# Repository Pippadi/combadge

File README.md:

# combadge [Work in Progress]

A Star Trek combadge built with the ESP32-S3.

> No copyright infringement is intended.
> This is simply a personal endeavor for fun and learning.

## Details

- Hardware and electronics: [hardware/pcb](hardware/pcb)
- Main ESP32 firmware: [software/combadge](software/combadge)
- Audio bridge: [software/bridge](software/bridge)
- 3D-printable enclosure: [hardware/enclosure](hardware/enclosure)
- Nuggets for testing: [software/test](software/test)
- Helpful scripts/tools: [software/tools](software/tools)

This is pretty much the entire directory tree. Happy exploring!

## Goals

Hardware has now been verified to work.

Some kind of basic walkie-talkie functionality is in the works, built on top of a custom Combadge Real-time Audio Protocol.
[WebRTC](https://webrtc.org) or [Matrix](https://matrix.org) support is a goal for the distant future.

Ahead of this, the roadmap is largely undecided. Capable hardware leaves great scope for software.

## Motivations

This is a hobby project I am pursuing in order to broaden my knowledge and experience with embedded electronics and programming.
And of course, to end up with a combadge better than the ones they used on TV (I believe those are just molded and painted resin).
Please bear in mind that I am a beginner, especially when it comes to the electronics (remember that before you plug the batteries in).

## Community

Suggestions, tips, and contributions are welcome!
I hope that with some (of your?) time and effort, this combadge can grow to become more useful than a block of resin, while still retaining the charm.

All the tools used for this, as mentioned in the READMEs, are free and open-source. Thank you to those that made this possible!

See also [DansDesigns/ComBadge](https://github.com/DansDesigns/ComBadge), a project with a similar theme and very intriguing prospects.

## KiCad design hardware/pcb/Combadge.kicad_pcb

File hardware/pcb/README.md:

# Electronics and PCB

See the [assets](assets) directory for screenshots of the schematics and PCB.

## Component Choices

The combadge is built around an [ESP32-S3-WROOM-1](https://www.espressif.com/en/support/download/documents/modules?keys=&field_type_tid%5B%5D=838).

I chose it because:

- It has hardware I2S and touch support
- It is well-supported by the Arduino toolchain
- It is cheaply available in my region

### Sound

I've chosen to adopt I2S peripherals for this project, as they promise better audio quality than their analog counterparts, while reducing the amount of analog circuitry I have to design.
The [ESP32-S3](https://docs.espressif.com/projects/esp-idf/en/latest/esp32s3/api-reference/peripherals/i2s.html) supports two I2S peripherals in hardware.

#### Microphone

I've zeroed in on the [Knowles SPH0645LM4H-1](https://www.knowles.com/docs/default-source/default-document-library/sph0645lm4h-1-datasheet.pdf?Status=Master&sfvrsn=751076b1_2).
Any similar microphone ought to do the job.

I use the INMP441 for prototyping because it's available as a module. I would have stuck with it for the PCB, but it seems to be discontinued by the manufacturer.

#### Speaker

The [Taoglas SPKM.10.8.A](https://www.taoglas.com/product/10-mm-round-miniature-speaker-500mw/) seems like an adequate speaker for the job.

A [MAX98357AETE+T](https://www.analog.com/en/products/max98357a.html#product-overview) class D amplifier drives the speaker.
It's what I use to prototype.

### Power Management

The unit runs on a lithium-polymer battery. Exact model and size undecided as of now. It will be one of the usual 3.7V LiPo cells.
All the chosen components of the combadge operate on 3.3V. I was hoping to find an all-in-one charging and voltage-regulating IC, but my searches yielded none for these parameters.

Charging is handled by an [MCP73831](https://www.microchip.com/en-us/product/MCP73831).
A 300mA [TLV74333PDBVR](https://www.ti.com/product/TLV743P/part-details/TLV74333PDBVR) LDO linear regulator provides 3.3V power.
A [TLV431AQFTA](https://www.diodes.com/assets/Datasheets/TLV431Q.pdf)-based circuit conditionally disables the regulator for battery over-discharge protection.

## PCB

The PCB has been designed in KiCAD.

- Footprints are chosen to be as large as possible where applicable, to facilitate hand-soldering or rework.
- The PCB has headers to which battery and speaker wires can be soldered.
- Certain measurements can be seen in the `User.Comments` layer.

This project makes use of the official Espressif [ESP32 KiCAD libraries](https://github.com/espressif/kicad-libraries).

You will need to change the paths to the third party symbols in the library and footprint managers. I've just plonked everything in a gitignored folder called `third-party`.

## Notes

### Crackling on speaker

When I was prototyping, I was powering everything off my computer's USB port. The INMP441 microphone module worked well, but the MAX98357 with no power supply filtering was horribly noisy.
Some beefy electrolytic capacitors reduced the noise, but did not eliminate it.

The root cause of the noise turned out to be the fact that I was powering the speaker through the AMS1117 3.3V regulator on my ESP32 dev board.
The regulator could not handle the current spikes demanded by the speaker, so its output voltage ended up dropping.
Hooking the speaker up directly to the USB 5V line (VIN on my particular dev board) solved the issue.

The PCB has been designed such that the amplifier is powered directly by the battery.
There are also some large low-transient-response-time ceramic capacitors for any bursts of energy components may need.

### SPH0645LM4H woes

The SPH0645 is known to have some quirks in its I2S interface, to do with the synchronization of the clock and data signals.
In addition, the signal it outputs has a weird offset from 0.

The required workaround for the first problem has been successfully implemented and the second is more of an annoyance.
Nevertheless, a future board revision may be better off with a more standard-compliant microphone like the ICS43434.

### Power stability during battery-less operation

The MCP73831 datasheet specifies a minimum value of 4.7uF for a capacitor across the battery side (C2 here) for stable supply when the battery is disconnected.
This is enough for the ESP32-S3 to boot, but not enough for more current-demanding tasks like turning on WiFi.
Future board revisions should have more and bigger capacitors to avoid brownouts when testing without a battery.

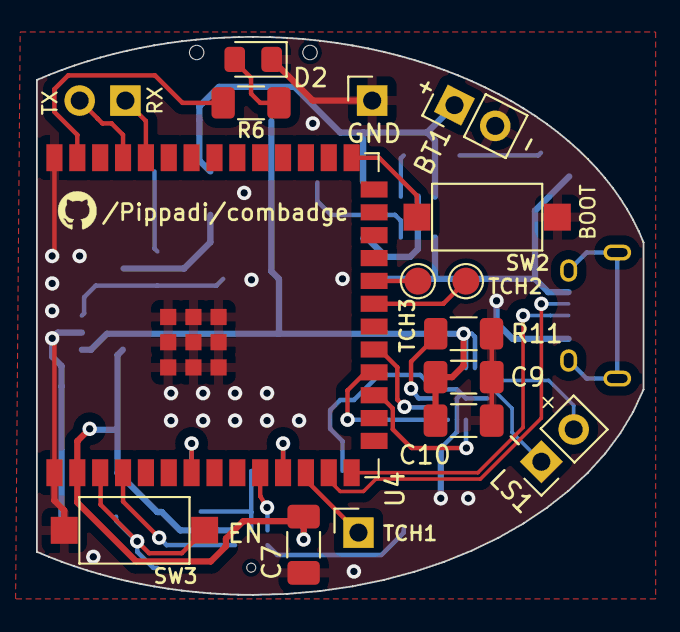
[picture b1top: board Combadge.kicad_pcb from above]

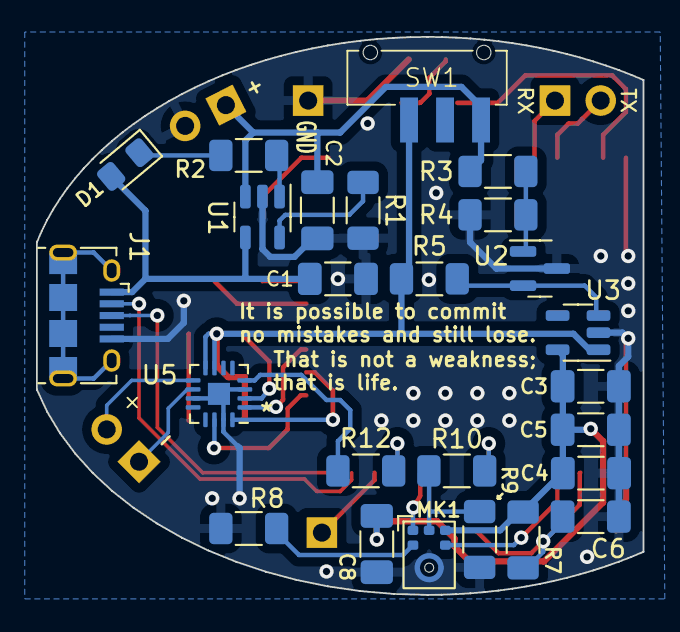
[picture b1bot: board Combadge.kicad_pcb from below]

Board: 2 copper layers, 33.7 x 31.0 mm, 41 parts (25 on the bottom side), 34 nets.

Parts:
BT1: Battery_Cell; PinHeader_1x02_P2.54mm_Vertical
C1, C2: 4.7uF; C_1206_3216Metric_Pad1.33x1.80mm_HandSolder
C3, C6, C7: 1uF; C_1206_3216Metric_Pad1.33x1.80mm_HandSolder
C4, C10: 10uF; C_1206_3216Metric_Pad1.33x1.80mm_HandSolder
C5, C9: 0.1uF; C_1206_3216Metric_Pad1.33x1.80mm_HandSolder
C8: 0.2uF; C_1206_3216Metric_Pad1.33x1.80mm_HandSolder
D1, D2: LED; LED_0805_2012Metric_Pad1.15x1.40mm_HandSolder
J1: USB_B_Micro; USB_Micro-B_Amphenol_10118194_Horizontal
J2: TOUCH1; PinHeader_1x01_P2.54mm_Vertical
J3: UART; PinHeader_1x02_P2.54mm_Vertical
J4: GND; PinHeader_1x01_P2.54mm_Vertical
LS1: Speaker; PinHeader_1x02_P2.54mm_Vertical
MK1: SPH0645LM4H; Knowles_SPH0645LM4H-6_3.5x2.65mm
R1: 4k; R_1206_3216Metric_Pad1.30x1.75mm_HandSolder
R2, R6: 150; R_1206_3216Metric_Pad1.30x1.75mm_HandSolder
R3: 220k; R_1206_3216Metric_Pad1.30x1.75mm_HandSolder
R4: 120k; R_1206_3216Metric_Pad1.30x1.75mm_HandSolder
R5, R7, R8: 10k; R_1206_3216Metric_Pad1.30x1.75mm_HandSolder
R9, R11: 100k; R_1206_3216Metric_Pad1.30x1.75mm_HandSolder
R10: 50; R_1206_3216Metric_Pad1.30x1.75mm_HandSolder
R12: 1k; R_1206_3216Metric_Pad1.30x1.75mm_HandSolder
SW1: SW_SPDT; CSS-1210TB
SW2: BOOT; SW_SPST_CK_RS282G05A3
SW3: EN; SW_SPST_CK_RS282G05A3
TP1: TOUCH2; TestPoint_Pad_D1.5mm
TP2: TOUCH3; TestPoint_Pad_D1.5mm
U1: MCP73831-2-OT; SOT-23-5
U2: TLV431AQFTA; SOT-23
U3: TLV73333PDBV; SOT-23-5
U4: ESP32-S3-WROOM-1
U5: MAX98357AETE+T; TQFN-16-1EP_3x3mm_P0.5mm_EP1.23x1.23mm

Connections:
+3.3V: C3.1, C4.2, C5.2, C7.2, C8.2, MK1.5 (VDD), R7.2, U3.5 (OUT), U4.2 (3V3)
+BATT: BT1.1 (+), C2.1, R3.2, SW1.3 (C), U1.3 (V_{BAT})
/ESP32/ESP_RX: J3.1, U4.36 (U0RXD/GPIO44/CLK_OUT2)
/ESP32/ESP_TX: J3.2, U4.37 (U0TXD/GPIO43/CLK_OUT1)
/ESP32/ESP_USB_D+: J1.3 (D+), U4.14 (GPIO20/U1CTS/ADC2_CH9/CLK_OUT1/USB_D+)
/ESP32/ESP_USB_D-: J1.2 (D-), U4.13 (GPIO19/U1RTS/ADC2_CH8/CLK_OUT2/USB_D-)
/ESP32/INDICATOR: D2.2 (A), R6.2
/ESP32/MIC_BCLK: MK1.4 (BCLK), U4.4 (GPIO4/TOUCH4/ADC1_CH3)
/ESP32/MIC_DATA: R10.2, U4.7 (GPIO7/TOUCH7/ADC1_CH6)
/ESP32/MIC_WS: MK1.1 (WS), U4.10 (GPIO17/U1TXD/ADC2_CH6)
/ESP32/SPK_BCLK: U4.18 (GPIO10/TOUCH10/ADC1_CH9/FSPICS0/FSPIIO4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), U5.16 (BCLK)
/ESP32/SPK_DATA: U4.19 (GPIO11/TOUCH11/ADC2_CH0/FSPID/FSPIIO5/S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), U5.1 (DIN)
/ESP32/SPK_EN: R12.2, U4.11 (GPIO18/U1RXD/ADC2_CH7/CLK_OUT3)
/ESP32/SPK_WS: U4.17 (GPIO9/TOUCH9/ADC1_CH8/FSPIHD/SUBSPIHD), U5.14 (LRCLK)
/ESP32/TOUCH1: J2.1, U4.12 (GPIO8/TOUCH8/ADC1_CH7/SUBSPICS1)
/ESP32/TOUCH2: TP1.1, U4.21 (GPIO13/TOUCH13/ADC2_CH2/FSPIQ/FSPIIO7/S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)
/ESP32/TOUCH3: TP2.1, U4.22 (GPIO14/TOUCH14/ADC2_CH3/FSPIWP/FSPIDQS/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)
/Power/CHRG_FULL: D1.1 (K), R2.2
/Speaker/SPK+: LS1.2, U5.9 (OUTP)
/Speaker/SPK-: LS1.1, U5.10 (OUTN)
BATT_AFTER_SWITCH: C9.2, C10.2, R5.1, SW1.2 (B), U3.1 (IN), U5.7 (VDD), U5.8 (VDD)
GND: BT1.2 (-), C1.2, C2.2, C3.2, C4.1, C5.1, C6.1, C7.1, C8.1, C9.1, C10.1, D2.1 (K), J1.5 (GND), J4.1, MK1.3 (GND), R1.2, R4.1, R8.2, R9.2, R11.1, SW2.1, SW3.1, U1.2 (V_{SS}), U2.3 (A), U3.2 (GND), U4.1 (GND), U4.40 (GND), U4.41 (GND), U5.3 (GND), U5.11 (GND), U5.15 (GND), U5.17 (Thermal)
unnamed: MK1.6 (DATA), R9.1, R10.1
unnamed: MK1.2 (SEL), R8.1
unnamed: R1.1, U1.5 (PROG)
unnamed: R2.1, U1.1 (STAT)
unnamed: R5.2, U2.2 (K), U3.3 (EN)
unnamed: R3.1, R4.2, U2.1 (REF)
unnamed: C6.2, R7.1, SW3.2, U4.3 (EN)
unnamed: SW2.2, U4.27 (GPIO0/BOOT)
unnamed: R6.1, U4.39 (GPIO1/TOUCH1/ADC1_CH0)
unnamed: R11.2, U5.2 (GAIN_SLOT)
unnamed: R12.1, U5.4 (SD_MODE)
VBUS: C1.1, D1.2 (A), J1.1 (VBUS), U1.4 (V_{DD})

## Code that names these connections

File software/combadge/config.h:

#include "driver/i2s.h"

/* Makefile automatically defines one of these symbols
   when defining SOC="esp32" or SOC="esp32s3" */
//#define SOC_ESP32
//#define SOC_ESP32_S3

#define LED 1

//#define MIC_INMP441
#define MIC_SPH0645

#define MIC_WS GPIO_NUM_17
#define MIC_DATA GPIO_NUM_7
#define MIC_BCLK GPIO_NUM_4

#define SPK_WS GPIO_NUM_9
#define SPK_DATA GPIO_NUM_11
#define SPK_BCLK GPIO_NUM_10
#define SPK_EN GPIO_NUM_18

typedef int16_t sample_t;
#define BYTES_PER_SAMPLE sizeof(sample_t)
#define BITS_PER_SAMPLE BYTES_PER_SAMPLE * 8

#define SAMPLE_RATE 44100

#define BUF_LEN_SAMPLES 256
#define BUF_LEN_BYTES BUF_LEN_SAMPLES * BYTES_PER_SAMPLE

#define BUF_FULL_INTERVAL_ms int(float(BUF_LEN_SAMPLES) * 1000.0 / float(SAMPLE_RATE))

#define WIFI_SSID "YourSSID"
#define WIFI_PASSWORD "YourPassword"

#define BRIDGE "192.168.8.100"
#define LISTEN_PORT 1701

#define TOUCH_PIN 8

#ifdef SOC_ESP32
#define TOUCH_THRESHOLD 30
#else
#define TOUCH_THRESHOLD 40000
#endif

// Milliseconds to wait after last recieved packet to assume that
// a transmission has "dropped" (stopped without AUDIO_STOP)
#define TX_DROP_TIMEOUT_MS 5000

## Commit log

2022-09-26 Initial commit for PCB
2022-09-26 Add readme for electronics and PCB
2022-09-26 Move hardware readme
2022-09-27 Add charging IC to schematic
2022-09-27 Add over-discharge protection circuit
2022-09-28 Add PCB footprint sources
2022-09-28 Add amplifier to schematic
2022-09-28 Connect I2S devices to ESP32
2022-09-28 Make ancillary ESP32 connections
2022-09-28 Add schematic titles
2022-09-28 Assign some footprints. Not done.
2022-09-29 Add some decoupling capacitors
2022-09-29 Finish footprint assignments (not final)
2022-09-29 Add basic PCB outline
2022-09-29 Route microphone
2022-09-29 Move incorrectly placed capacitors around microphone
2022-09-29 Route speaker and amplifier
2022-10-01 Finish initial version of PCB
2022-10-01 Change ground plane to reduce stray capacitances
2022-10-07 Add PCB cutout SVG
2022-10-08 Fix some DRC errors
2022-10-08 Fix more DRC errors and reconnect broken routes
2022-10-08 Add labels to pins
2022-10-08 Update PCB picture for readme
2022-10-09 Replace Nuvoton amplifier with MAX98357
2022-10-09 Add MAX98357 to PCB
2022-10-10 Cleanup tracks
2022-10-10 Fix clearance error with BGA pad route
2022-10-11 Move silkscreen legends around
2022-10-11 Fix more DRC errors
2022-10-11 Update documentation
2022-10-13 Redo fill zones
2022-10-13 Tell DRC to ignore courtyard defects
2022-10-14 Remove unused custom symbols and footprints
2022-10-22 Make PCB documentation nicer to read
2022-10-22 Get microphone data to transmit over UDP
2022-10-22 Add personal secrets to combadge.ino. DO NOT PUSH.
2022-10-22 Break things into more manageable files
2022-10-22 Move WiFi credentials to config.h
2022-10-22 Put secrets in config.h. DO NOT PUSH.
2022-10-30 Add UDP listener test program
2022-10-30 Enable basic speaker functionality
2022-11-22 Add power switch and redo overdischarge circuit
2022-11-28 Rework overdischarge protection
2022-11-28 Replace transistor network with RN4989 in overdischarge circuit
2022-11-29 Add power switch and rework header placement
2022-11-30 Pretty things up a bit
2023-01-31 Add program to test MAX98375 amplifier
2023-01-31 Switch to ESP-IDF driver from Arduino abstraction for I2S
2023-01-31 Add typedef for easy sample size switching
2023-01-31 Add READMEs to test code
2023-01-31 Correctly report buffer size in bytes
2023-01-31 Change I2S comm format to match Philips standard as specified in MAX98357 datasheet
2023-02-02 Update speaker to use tested working config
2023-02-02 Secret password update. Do not push.
2023-02-03 Replace two constants with one
2023-02-04 Update microphone I2S config
2023-02-04 Revert "Merge commit '233b' into code-dev"
    This reverts commit 61eccbea9441850d184a7fe73d19577349dae08b, reversing
    changes made to f4d8feada8c73089aabe5871204545ee146937a6.
2023-02-05 Add test for playing sound clips
2023-02-08 Match sound clip sample rate to playback sample rate
2023-02-10 Add sound file to header file tool
2023-02-10 Add sound files to main program
2023-02-10 Test playSound
2023-02-11 Create class for MAX98375
2023-02-11 Create class for INMP441
2023-02-11 Remove vestigial file
2023-02-11 Flatten edge of PCB where micro USB port sits
2023-02-11 Reduce number of net classes and trace widths
2023-02-11 Remove warning about unconnected pad
2023-02-12 Update pins to to match PCB
2023-02-12 Fix USP-6B07 footprint
2023-02-12 Update audio header generator tool to allow for different sample resolutions
2023-02-12 Fix small formatting annoyance
2023-02-13 Get started on enclosure
2023-02-15 Create chevron SVG from bitmap
2023-02-15 Put chevron in 3D model
2023-02-17 Start enclosure from scratch.
    Create only main base.
2023-02-17 Revert "Start enclosure from scratch."
    This reverts commit 32f4118cdb9fcf8692dbca84793f07212d7b7ac6.
2023-02-17 Start over with enclosure, getting measurements right (I hope)
2023-02-17 Add rim to base
2023-02-17 Add curvature to top of base
2023-02-17 Add chevron
2023-02-17 Update README with enclosure picture
2023-02-20 Miscellaneous minor improvements
2023-03-01 Get started with test for INMP441 microphone
    Not done yet.
2023-03-01 Bump KiCad version to 7
2023-03-02 Replace XC6808 with MCP73831 in schematic
2023-03-02 Remove XC6808 from documentation
2023-03-02 Add MCP73831 to PCB
2023-03-02 Use single resistor for setting amplifier gain
2023-03-02 Cleanup silkscreen
2023-03-03 Remove unused custom symbol and footprint
    Why didn't I do this earlier?
2023-03-03 Add indicator LED
2023-03-06 Replace zener diode setup with TLV431
2023-03-06 Make all resistors 1206 and LEDs 0805
2023-03-07 Switch to TLV4333PDBVR LDO regulator
2023-03-07 Update README with updated component choices
2023-03-10 Replace BGA IC with QFN
2023-03-10 Update footprints to get rid of DRC error
2023-03-11 Fix broken link in readme
2023-03-11 Get INMP441 to work
2023-03-11 Cleanup INMP441 read
2023-03-12 Add function to check for max98357 sleep state
2023-03-13 Replace chevron with one closer to the one shown on TV
2023-03-14 Make speaker enabling and disabling a little smoother
2023-03-14 Make sound clip playback simpler
2023-03-14 Make sound playback work again
2023-03-14 Update sound clip header generator tool
2023-03-14 Update enclosure picture
2023-03-15 Have speaker playback take place in another thread
2023-03-15 Make I2S DMA buffers as big as possible
2023-03-15 Move transmission of microphone data to another thread
2023-03-15 Update documentation (for real this time)
2023-03-17 Add touch to toggle
2023-03-17 Tweak for maximum clarity for sound playback
2023-03-17 Add some basic power-saving measures
2023-03-19 Add relevant measurements to PCB
2023-03-20 Add ESP32 boot button
2023-03-20 Import KiCad-generated 3D model to blender
2023-03-20 Make cavity for electronics 1cm deep
2023-03-31 Make chevron bigger
2023-04-03 Add cutouts for power switch and micro USB port
2023-04-03 Rotate PCB by 180 degrees
2023-04-04 Pre-fab changes
2023-04-06 Change byte order when recording from INMP441
2023-04-08 Get some kind of audio out of the INMP441
2023-04-09 Get discernible words out of microphone
2023-04-10 Rework INMP441 read function
2023-04-11 Miscellaneous cleanup
2023-04-11 Return correct number of samples recorded
2023-04-12 Record crystal clear audio
2023-04-13 Add test for streaming microphone data over TCP
2023-04-16 Rewire power switch so that the unit can be turned on
    Thank you to Reddit user justadiode.
2023-04-20 Remove acute angles from PCB copper layers
2023-04-24 Cleanup schematic to follow convention
    Thanks to Reddit users Crazy_Direction_1084 and AgentiMi for introducing
    me to this.
2023-04-24 Update PCB from updated schematic
2023-04-24 Replace third party MAX98357 symbol with custom one
2023-04-26 Add ground pours
    Thanks to Reddit user AgentiMi for the recommendation
2023-04-26 Break out ESP enable pin
2023-04-26 Replace stand-in symbol with custom one for TLV431
2023-04-27 More silkscreen cleanup
2023-05-07 Replace ESP32 with ESP32-S3
2023-05-14 Add pictures of schematic and PCB
2023-05-18 Add test for streaming audio data over TCP to MAX98357
2023-05-18 Revert "Add test for streaming audio data over TCP to MAX98357"
    This reverts commit d88ba64b8451a7f6b7af6247099f9c6e46fe6a44.
2023-05-18 Simplify writing to MAX98357
2023-05-20 Power speaker amplifier directly from battery
    Also increase power trace widths
2023-05-20 Update documentation on speaker noise reduction
2023-05-21 Ensure speaker playback continues even after combadge chirps to start recording
2023-05-21 Ensure a single touch doesn't register twice
2023-05-24 Make copper pour cover entire surface of board
2023-06-05 Update images
2023-06-17 Replace EOL CUI devices microphone with Knowles SPH0645
2023-06-26 Get started on OpenSCAD-based 3D model
2023-06-26 Add extra touch pads
2023-06-29 Link to project GitHub on silkscreen
2023-06-29 Fix badly positioned pin in MAX98357 symbol
2023-06-30 Exclude unpopulated connectors from BOM
2023-06-30 Use noncritical GPIO pins for I2S peripherals
2023-06-30 Rewire charge indicator LED
2023-06-30 Increase track clearance
2023-07-01 Fix silkscreen snafu
2023-07-01 Finish final once-over
2023-07-11 Replace third-party switch footprint with custom
2023-07-17 Add quick-and-dirty dummy combadge tool
2023-07-21 Add start and stop packets
2023-07-21 Add some macros for convenience
2023-07-21 Get started with bridge
2023-07-22 Use structs to handle metadata
2023-07-22 Smoothly read audio data packets
2023-07-23 Move assembly of fragments to a separate function
2023-07-24 Divide functionality among actors
2023-07-24 Unmarshal incoming packets to structs
2023-07-24 Get actor-based bridge to a non-crashing (but nonfunctional) state
2023-08-14 Add functional-enough SPH0654 test
2023-08-25 Record crystal-clear audio from the SPH0645
2023-08-27 Initial support for SPH0645 [Untested]
2023-09-22 Add preliminary CRAP support to dummy combadge [Untested]
2023-09-24 Figure out touch on ESP32-S3
2023-09-29 Prevent sole transmitter from being regarded as another receiver
2023-10-11 Ensure a transmitting badge actually registers as transmitting
2023-11-05 Ensure transmissions end properly
2023-11-12 Avoid reading buffered values beyond sent size
2023-11-12 Create initial Fourier transform test script
2023-12-18 Allow Fourier transform script to read from sound file
2023-12-18 Limit number of samples read for Fourier transform test
2023-12-23 Add textured top to base
2023-12-24 Rework base and cavity
2023-12-24 Fix cavity
2023-12-26 Make space for power switch
2023-12-31 Add backplate
2023-12-31 Add snap clips to backplate
2024-01-01 Add slots for snap clips
2024-01-07 First actual print
2024-01-07 Update image in README
2024-01-10 Rename fourierTransform to fourierAnalysis for accuracy
2024-01-28 Add Makefile
2024-01-28 Clean up imports
2024-02-17 Reduce buffer size for smaller packets
2024-02-17 Reduce packet size to 256 samples for more reliable throughput
2024-02-17 Improve bad packet handling
2024-02-17 Allow graceful dropping of transmissions
2024-02-17 Improve transmission drop handling
2024-02-17 Read speaker data chunk by chunk
2024-02-17 Don't read the start of the next packet when reading speaker data
2024-02-18 Add build and flash instructions
2024-08-11 Use new I2S driver
    Untested.
2024-10-16 Update SPH0645 test to use new I2S driver
2024-10-16 Use SPH0645 with reg manipulation and new driver
    Recorded audio still garbled for some reason.
2024-10-19 Get started with custom ringbuf
2024-10-19 Make ringbuf build
2024-10-20 Add functions to read and write slices
    Unoptimized for now.
2024-10-20 Sum written values from different writers
2024-10-20 Handle underflows
2024-10-20 Ensure write offsets never go negative
2024-10-20 Add mutex for thread safety
2024-10-20 Switch to ringbuf-based mixer
2024-10-20 Use standard function for reading full buffer
2024-10-20 Don't buffer and then copy so much
2024-10-20 Fix minimum transmission size logic
2024-11-08 Add simple recorder tool
2024-11-08 Pin speaker and mic tasks to different cores
    Lowers contention for CPU time and clears up microphone recording
    quality.
2024-12-08 Begin migration to ESP-IDF
    Untested. Almost certainly doesn't work.
2025-01-08 Move WiFi management to ESP IDF functions
2025-01-08 Use C++ file extensions
2025-01-26 Clear up a lot of ESP IDF migration related-errors
    Still broken.
2025-01-26 Make stuff build
2025-01-26 Stop crashing on WiFi init
2025-02-01 Update CMake configs
2025-02-02 Use IDF touch API
    Compiles; untested.
2025-08-18 Pare down main program for testing
